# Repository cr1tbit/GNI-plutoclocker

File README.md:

# GNI-plutoclocker

This device serves a couple of roles:
* allowing clocking adalm-pluto by an external clock source of broad frequency range
* injecting clock signal into RF trace, for clocking modded LNB
* supplying LNB with DC voltage (12v/18v selectable with an external switch)
* additional clock output

The device is based on CDCE913 which is a neat 3-output clock source generator. It has an excillent, low jitter PLL inside, and has been tested to work well with an OCXO for the purpose of communication via OSCAR-100 satellite.

## Configuration

The device is programmed via I2C rail. The proper register values may be programmed, using an arduino sketch ( available in this repo).

More about this project may be found on https://hf5l.pl/en/adalm-pluto-clocker-2/

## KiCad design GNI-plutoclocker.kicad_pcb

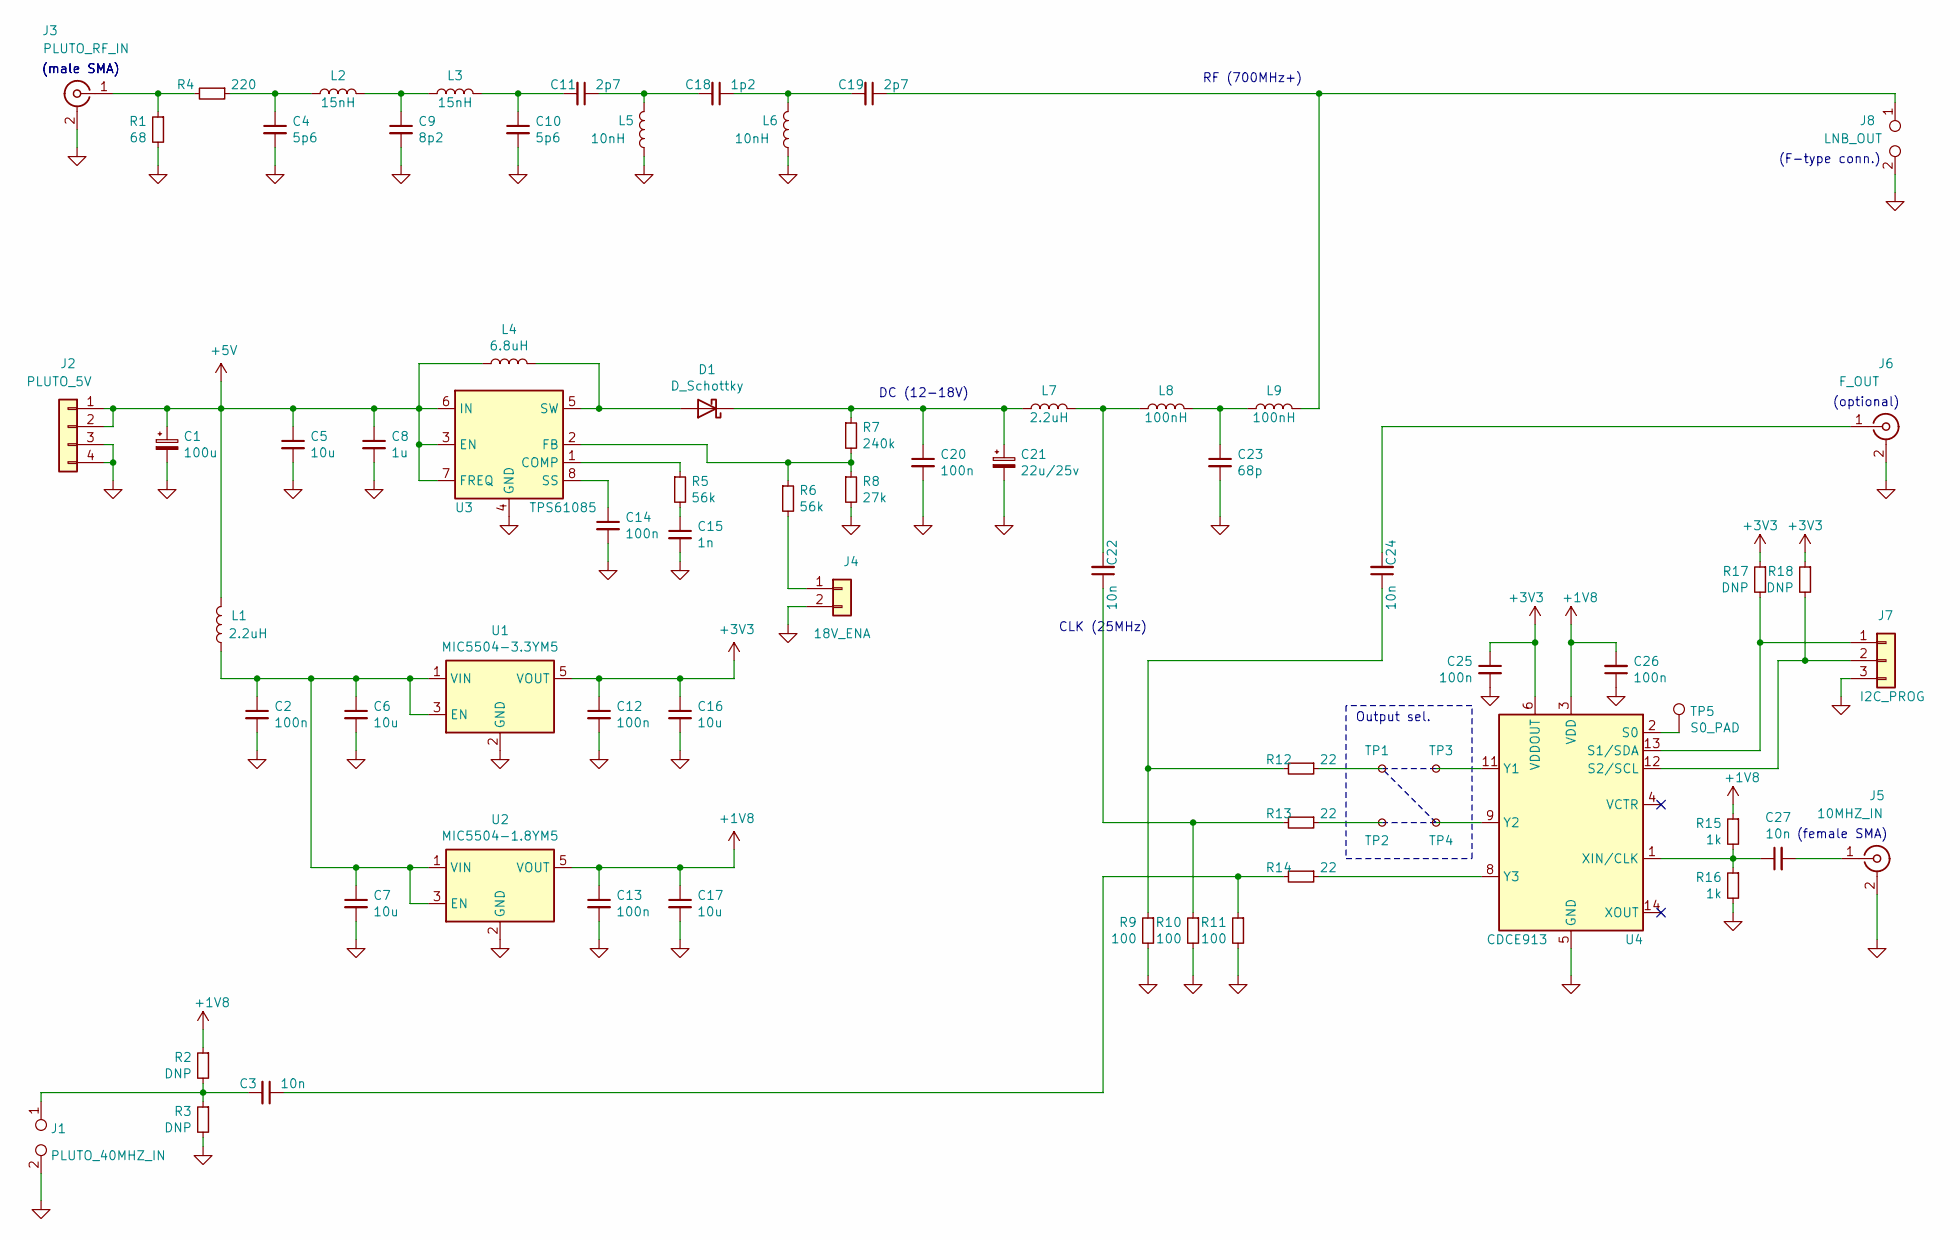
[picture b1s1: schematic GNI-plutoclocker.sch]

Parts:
C1: 100u; CP_Radial_D8.0mm_P3.80mm
C2, C12, C13, C14, C20, C25, C26: 100n; C_0805_2012Metric
C3, C22, C24, C27: 10n; C_0805_2012Metric
C4, C10: 5p6; C_0805_2012Metric
C5, C6, C7, C16, C17: 10u; C_0805_2012Metric
C8: 1u; C_0805_2012Metric
C9: 8p2; C_0805_2012Metric
C11, C19: 2p7; C_0805_2012Metric
C15: 1n; C_0805_2012Metric
C18: 1p2; C_0805_2012Metric
C21: 22u/25v; CP_Radial_D8.0mm_P3.80mm
C23: 68p; C_0805_2012Metric
D1: D_Schottky; D_SMA
J1: PLUTO_40MHZ_IN; TestPoint_2Pads_Pitch2.54mm_Drill0.8mm
J2: PLUTO_5V; PinSocket_1x04_P2.54mm_Vertical
J3: PLUTO_RF_IN; SMA_Samtec_SMA-J-P-X-ST-EM1_EdgeMount
J4: 18V_ENA; TestPoint_2Pads_Pitch2.54mm_Drill0.8mm
J5: 10MHZ_IN; SMA_Samtec_SMA-J-P-X-ST-EM1_EdgeMount
J6: F_OUT; SMA_Samtec_SMA-J-P-X-ST-EM1_EdgeMount
J7: I2C_PROG; PinSocket_1x03_P2.54mm_Vertical
J8: LNB_OUT; TestPoint_2Pads_Pitch2.54mm_Drill0.8mm
L1, L7: 2.2uH; L_0805_2012Metric_Pad1.15x1.40mm_HandSolder
L2, L3: 15nH; L_0805_2012Metric_Pad1.15x1.40mm_HandSolder
L4: 6.8uH; L_Fastron_PISN_Handsoldering
L5, L6: 10nH; L_0805_2012Metric_Pad1.15x1.40mm_HandSolder
L8, L9: 100nH; L_0805_2012Metric_Pad1.15x1.40mm_HandSolder
R1: 68; R_0805_2012Metric
R2, R3, R17, R18: DNP; R_0805_2012Metric
R4: 220; R_0805_2012Metric
R5, R6: 56k; R_0805_2012Metric
R7: 240k; R_0805_2012Metric
R8: 27k; R_0805_2012Metric
R9, R10, R11: 100; R_0805_2012Metric
R12, R13, R14: 22; R_0805_2012Metric
R15, R16: 1k; R_0805_2012Metric
TP1, TP2, TP3, TP4: TestPoint_Small; TestPoint_Pad_D1.0mm
TP5: S0_PAD; TestPoint_Pad_D1.0mm
U1: MIC5504-3.3YM5; SOT-23-5
U2: MIC5504-1.8YM5; SOT-23-5
U3: TPS61085; TSSOP-8_4.4x3mm_P0.65mm
U4: CDCE913; TSSOP-14_4.4x5mm_P0.65mm

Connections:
+1V8: C13.1, C17.1, C26.2, R2.1, R15.1, U2.5 (VOUT), U4.3 (VDD)
+3V3: C12.1, C16.1, C25.1, R17.1, R18.1, U1.5 (VOUT), U4.6 (VDDOUT), U4.7 (VDDOUT)
+5V: C1.1, C5.1, C8.1, J2.1, J2.2, L1.2, L4.1, U3.3 (EN), U3.6 (IN), U3.7 (FREQ)
GND: C1.2, C2.2, C4.2, C5.2, C6.2, C7.2, C8.2, C9.2, C10.2, C12.2, C13.2, C14.2, C15.2, C16.2, C17.2, C20.2, C21.2, C23.2, C25.2, C26.1, J1.2, J2.3, J2.4, J3.2 (Ext), J4.2, J5.2 (Ext), J6.2 (Ext), J7.3, J8.2, L5.1, L6.1, R1.2, R3.2, R8.2, R9.2, R10.2, R11.2, R16.2, U1.2 (GND), U2.2 (GND), U3.4 (GND), U4.5 (GND), U4.10 (GND)
unnamed: C2.1, C6.1, C7.1, L1.1, U1.1 (VIN), U1.3 (EN), U2.1 (VIN), U2.3 (EN)
unnamed: C3.1, R11.1, R14.2
unnamed: C3.2, J1.1, R2.2, R3.1
unnamed: C4.1, L2.1, R4.1
unnamed: C9.1, L2.2, L3.1
unnamed: C10.1, C11.2, L3.2
unnamed: C11.1, C18.2, L5.2
unnamed: C14.1, U3.8 (SS)
unnamed: C15.1, R5.2
unnamed: C18.1, C19.2, L6.2
unnamed: C19.1, J8.1, L9.2
unnamed: C20.1, C21.1, D1.1 (K), L7.1, R7.1
unnamed: C22.1, R10.1, R13.2
unnamed: C22.2, L7.2, L8.1
unnamed: C23.1, L8.2, L9.1
unnamed: C24.1, R9.1, R12.2
unnamed: C24.2, J6.1 (In)
unnamed: C27.1, R15.2, R16.1, U4.1 (XIN/CLK)
unnamed: C27.2, J5.1 (In)
unnamed: D1.2 (A), L4.2, U3.5 (SW)
unnamed: J3.1 (In), R1.1, R4.2
unnamed: J4.1, R6.2
unnamed: J7.1, R17.2, U4.13 (S1/SDA)
unnamed: J7.2, R18.2, U4.12 (S2/SCL)
unnamed: R5.1, U3.1 (COMP)
unnamed: R6.1, R7.2, R8.1, U3.2 (FB)
unnamed: R12.1, TP1.1
unnamed: R13.1, TP2.1
unnamed: R14.1, U4.8 (Y3)
unnamed: TP3.1, U4.11 (Y1)
unnamed: TP4.1, U4.9 (Y2)
unnamed: TP5.1, U4.2 (S0)

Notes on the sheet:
RF (700MHz+)
DC (12-18V)
CLK (25MHz)
(male SMA)
(F-type conn.)
(female SMA)
(optional)
Output sel.

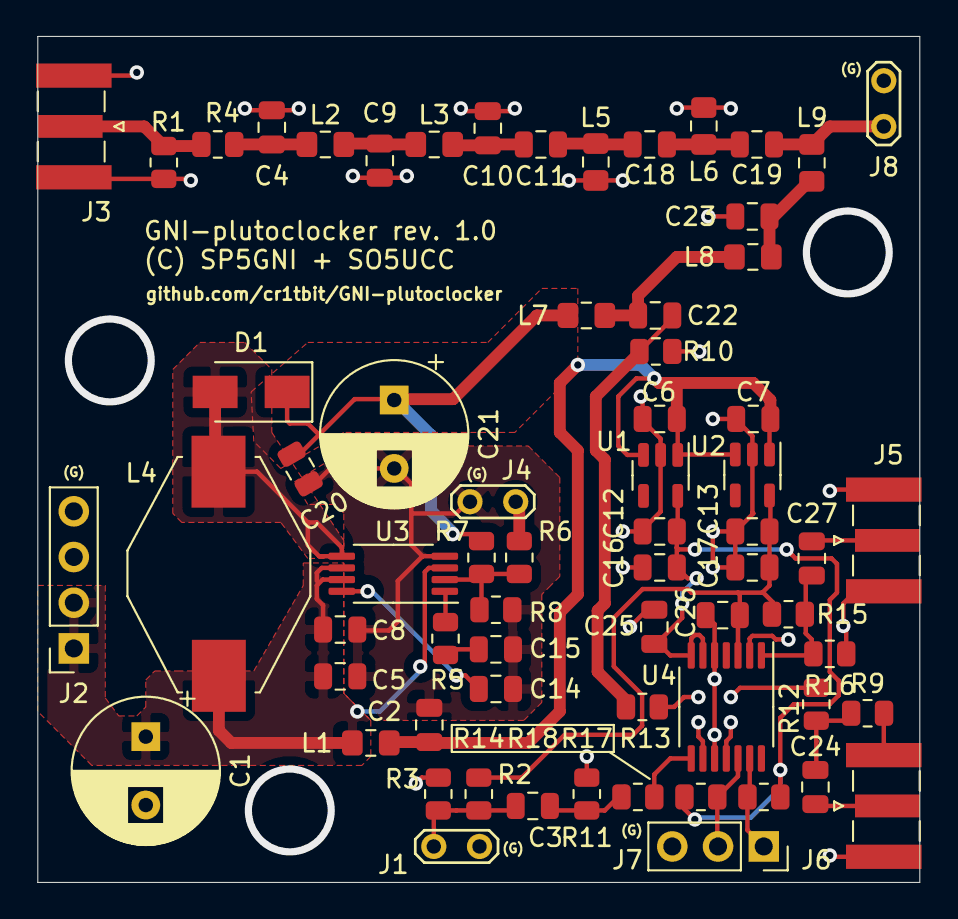
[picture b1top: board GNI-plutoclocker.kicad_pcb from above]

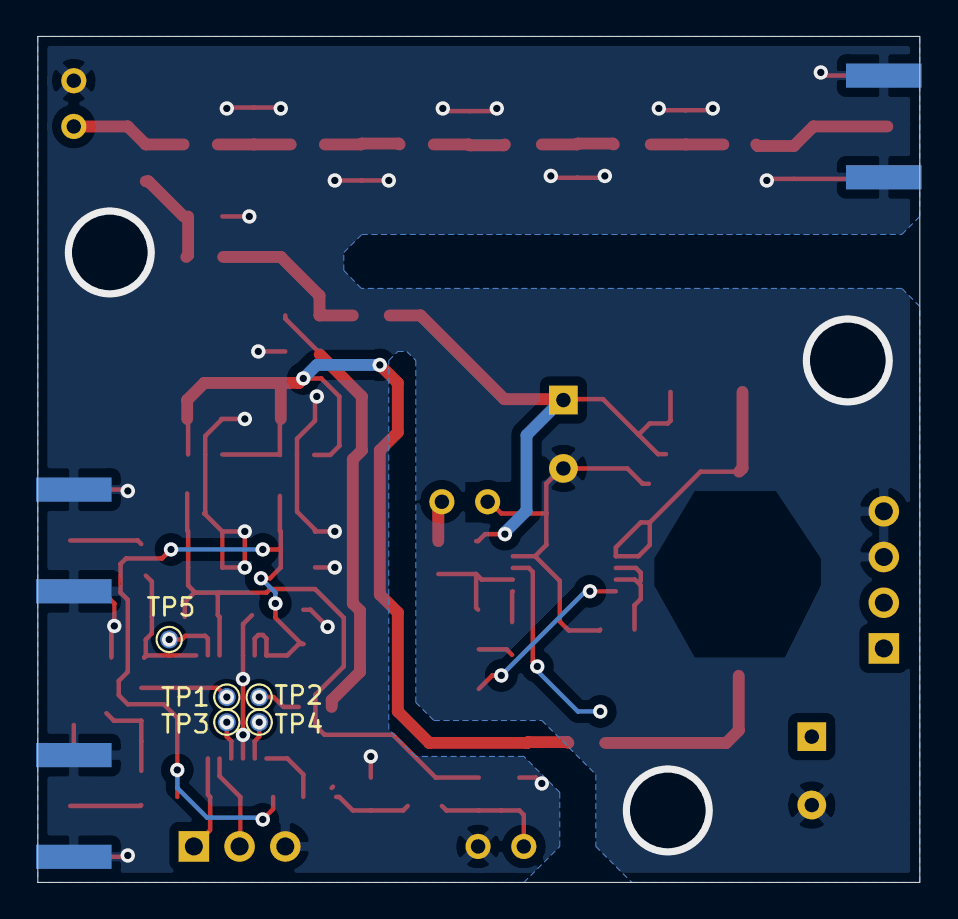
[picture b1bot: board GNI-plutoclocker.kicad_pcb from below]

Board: 2 copper layers, 49.0 x 47.0 mm, 72 parts (5 on the bottom side), 36 nets.

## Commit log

2020-11-24 adding PDF schematic
2020-12-16 adding firmware for chip programming
2020-12-16 adding some project changes and fab outputs
2020-12-19 setting proper clock outputs for the chip
2020-12-19 minor aesthetics schematics and silk layer adjustments
2020-12-19 adding 3d view image
2020-12-24 adding a photo to the repo
2020-12-25 adding BOM file
2021-05-01 next revision candidate - adding some solderbridge multiplexing options
